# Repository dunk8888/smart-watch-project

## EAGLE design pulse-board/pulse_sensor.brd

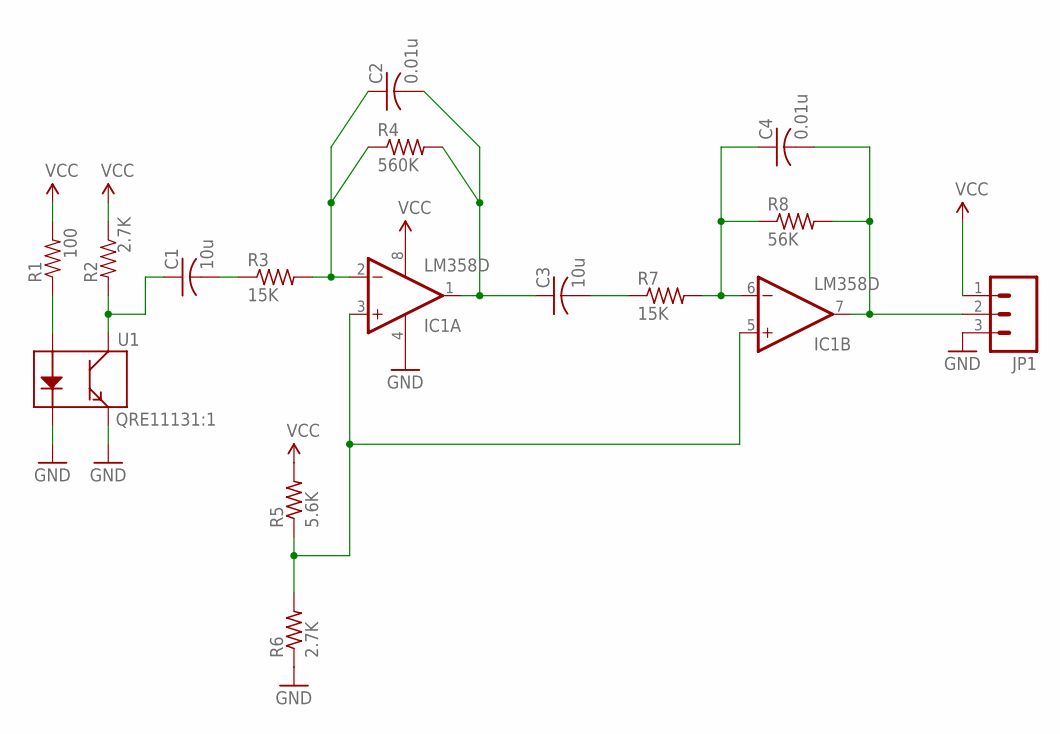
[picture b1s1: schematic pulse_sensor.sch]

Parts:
C1, C3: 10u; C0603
C2, C4: 0.01u; C0603
IC1: LM358D; SO08
JP1: M03PTH; 1X03
R1: 100; 0603-RES
R2: 2.7K; 0603-RES
R3, R7: 15K; R0603
R4: 560K; R0603
R5: 5.6K; R0603
R6: 2.7K; R0603
R8: 56K; R0603
U1: QRE11131:1; QRE1113-1:1

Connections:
GND: IC1.4 (V-), JP1.3, R6.1, U1.2 (K), U1.4 (E)
unnamed: R1.1, U1.1 (A)
unnamed: C2.1, IC1.2 (-IN), R3.2, R4.1
unnamed: C1.2, R3.1
unnamed: C2.2, C3.1, IC1.1 (OUT), R4.2
unnamed: C3.2, R7.1
unnamed: C4.1, IC1.6 (-IN), R7.2, R8.1
unnamed: C4.2, IC1.7 (OUT), JP1.2, R8.2
unnamed: IC1.3 (+IN), IC1.5 (+IN), R5.1, R6.2
OUT: C1.1, R2.2, U1.3 (C)
VCC: IC1.8 (V+), JP1.1, R1.2, R2.1, R5.2

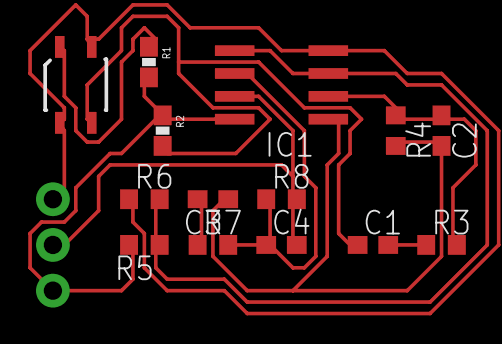
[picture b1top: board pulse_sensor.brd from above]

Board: 2 copper layers, 15 parts (1 on the bottom side), 11 nets.

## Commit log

2015-05-20 initial submission
2015-05-24 simple serial console almost the same as u8glib console program
2015-05-27 pulse detector by IR photo-interrupter
